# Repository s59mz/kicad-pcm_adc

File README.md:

# pcm_adc_pmod
PCM1808 ADC Testing module with PMOD interface

Schematic:
[pcm_pmod.pdf](pcm_pmod.pdf)

BOM:
[pcm_pmod.csv](pcm_pmod.csv)

Gerbers:
[gerbers.zip](https://github.com/s59mz/kicad-pcm_adc/raw/main/gerbers.zip)

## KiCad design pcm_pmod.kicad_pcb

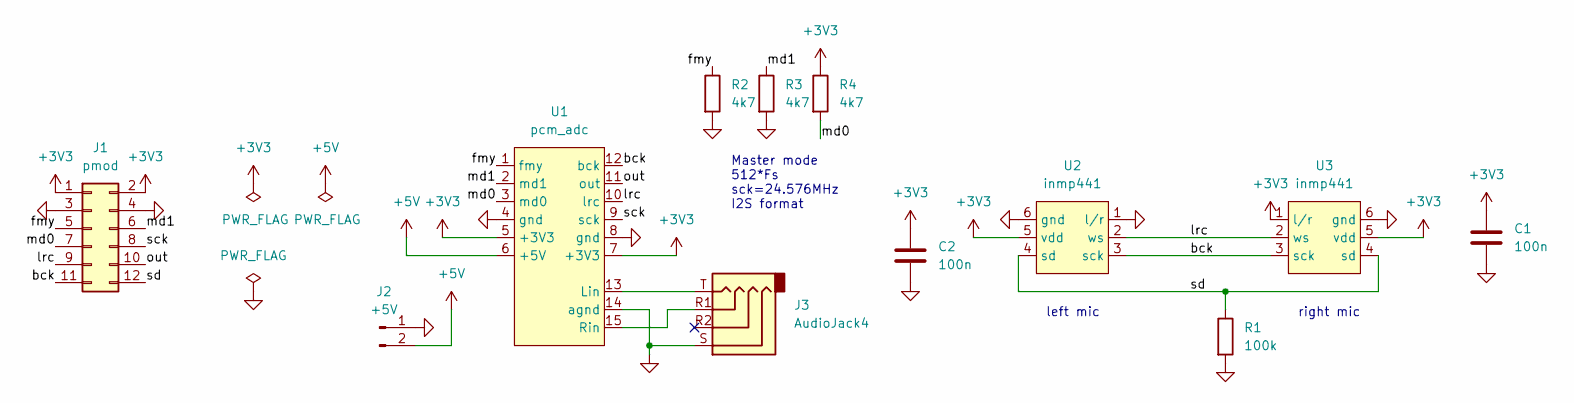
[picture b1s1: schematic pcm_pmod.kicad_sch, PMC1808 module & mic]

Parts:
C1, C2: 100n; C_0603_1608Metric_Pad1.08x0.95mm_HandSolder
J1: pmod; PinHeader_2x06_P2.54mm_Horizontal
J2: +5V; PinHeader_1x02_P2.54mm_Vertical
J3: AudioJack4; Jack_3.5mm_PJ320D_Horizontal
R1: 100k; R_0603_1608Metric_Pad0.98x0.95mm_HandSolder
R2, R3, R4: 4k7; R_0603_1608Metric_Pad0.98x0.95mm_HandSolder
U1: pcm_adc
U2, U3: inmp441; inmp441-module

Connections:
+3V3: C1.1, C2.1, J1.1, J1.2, R4.1, U1.5 (+3V3), U1.7 (+3V3), U2.5 (vdd), U3.1 (l/r), U3.5 (vdd)
+5V: J2.2, U1.6 (+5V)
/bck: J1.11, U1.12 (bck), U2.3 (sck), U3.3 (sck)
/fmy: J1.5, R2.1, U1.1 (fmy)
/lrc: J1.9, U1.10 (lrc), U2.2 (ws), U3.2 (ws)
/md0: J1.7, R4.2, U1.3 (md0)
/md1: J1.6, R3.1, U1.2 (md1)
/out: J1.10, U1.11 (out)
/sck: J1.8, U1.9 (sck)
/sd: J1.12, R1.1, U2.4 (sd), U3.4 (sd)
GND: C1.2, C2.2, J1.3, J1.4, J2.1, J3.S, R1.2, R2.2, R3.2, U1.4 (gnd), U1.8 (gnd), U1.14 (agnd), U2.1 (l/r), U2.6 (gnd), U3.6 (gnd)
unnamed: J3.R1, U1.15 (Rin)
unnamed: J3.T, U1.13 (Lin)

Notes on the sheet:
left mic
right mic
Master mode 512*Fs sck=24.576MHz I2S format

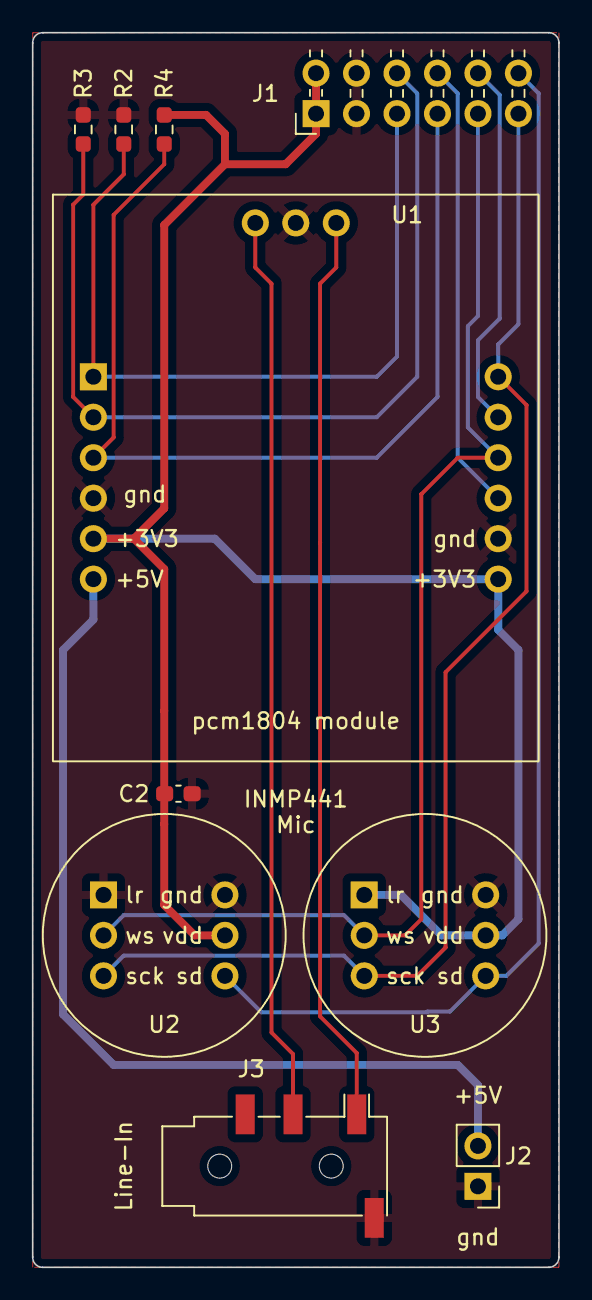
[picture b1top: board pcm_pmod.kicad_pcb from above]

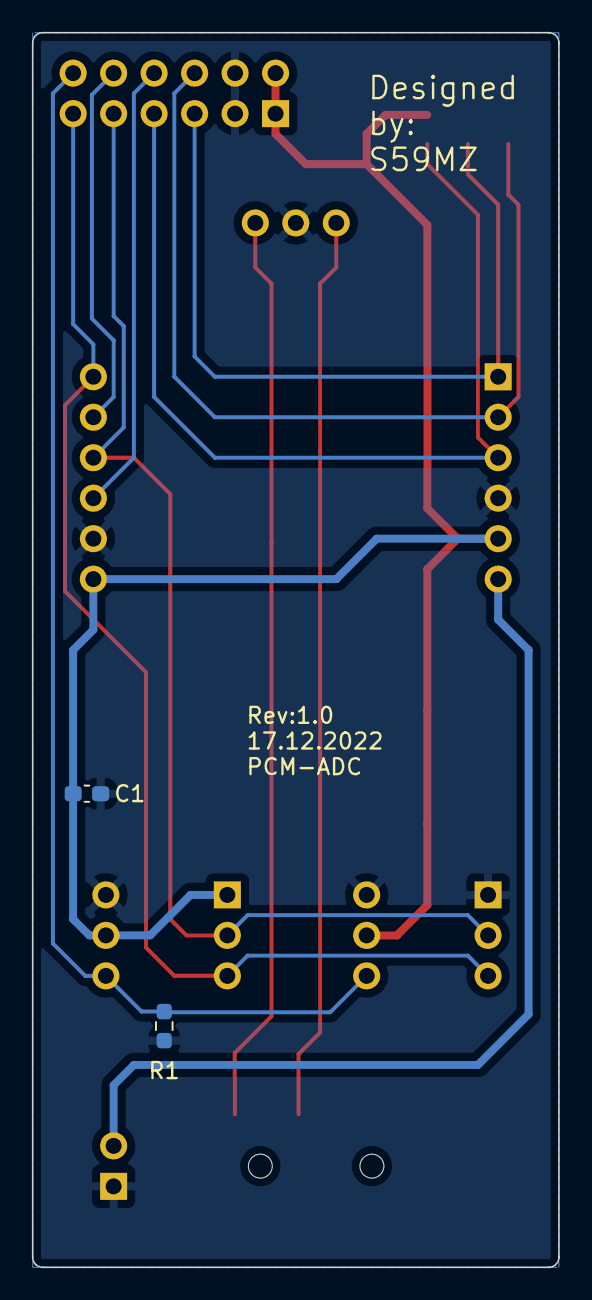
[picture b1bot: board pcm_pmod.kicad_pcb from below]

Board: 2 copper layers, 33.0 x 77.5 mm, 12 parts (2 on the bottom side), 13 nets.

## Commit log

2024-08-11 add screenshots
